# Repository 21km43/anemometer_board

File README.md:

# Anemometer board

# Requirements

- [KiCAD 9.0](https://kicad.org)
- [ESP32-C3-DevBoard](https://github.com/21km43/ESP32-C3-DevBoard)

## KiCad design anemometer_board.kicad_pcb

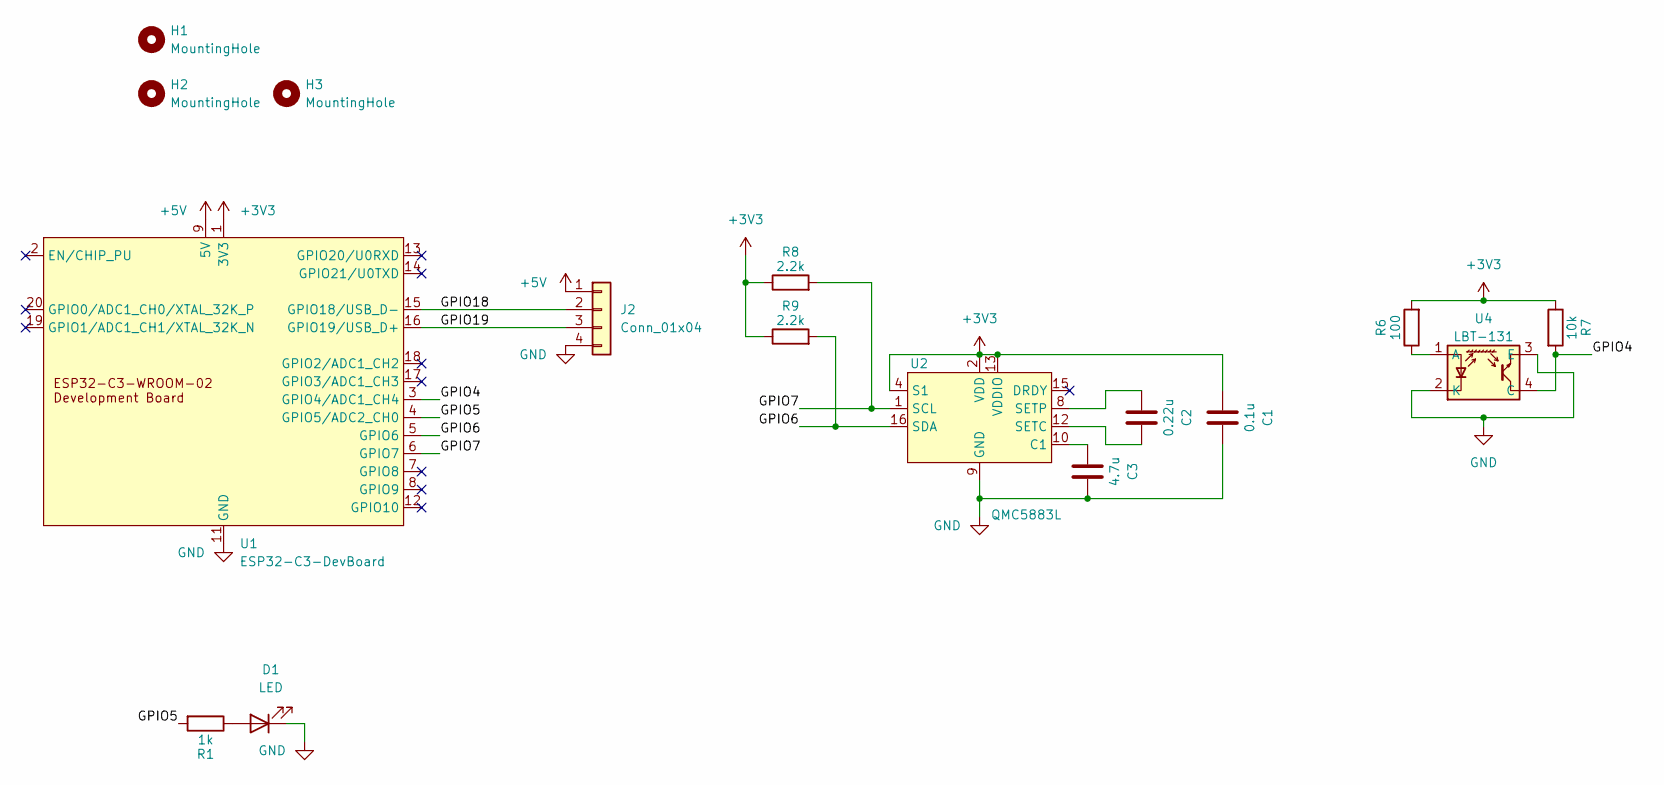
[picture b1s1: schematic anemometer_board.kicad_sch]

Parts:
C1: 0.1u; C_0402_1005Metric; LCSC C1525
C2: 0.22u; C_0402_1005Metric; LCSC C16772
C3: 4.7u; C_0402_1005Metric; LCSC C23733
D1: LED; LED_D5.0mm
H1, H2, H3: MountingHole; MountingHole_3.2mm_M3
J2: Conn_01x04; JST_XH_S4B-XH-A_1x04_P2.50mm_Horizontal
R1: 1k; R_Axial_DIN0207_L6.3mm_D2.5mm_P7.62mm_Horizontal; LCSC C11702
R6: 100; R_Axial_DIN0207_L6.3mm_D2.5mm_P10.16mm_Horizontal; LCSC C25076
R7: 10k; R_Axial_DIN0207_L6.3mm_D2.5mm_P10.16mm_Horizontal; LCSC C25744
R8, R9: 2.2k; R_0402_1005Metric; LCSC C25879
U1: ESP32-C3-DevBoard
U2: QMC5883L; LGA-16_3x3mm_P0.5mm; LCSC C976032
U4: LBT-131

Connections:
+3V3: C1.1, R6.2, R7.1, R8.1, R9.1, U1.1 (3V3), U2.2 (VDD), U2.4 (S1), U2.13 (VDDIO)
+5V: J2.1, U1.9 (5V)
/GPIO4: R7.2, U1.3 (GPIO4/ADC1_CH4), U4.4 (C)
/GPIO5: R1.2, U1.4 (GPIO5/ADC2_CH0)
/GPIO6: R9.2, U1.5 (GPIO6), U2.16 (SDA)
/GPIO7: R8.2, U1.6 (GPIO7), U2.1 (SCL)
/GPIO18: J2.2, U1.15 (GPIO18/USB_D-)
/GPIO19: J2.3, U1.16 (GPIO19/USB_D+)
GND: C1.2, C3.2, D1.1 (K), J2.4, U1.10 (GND), U1.11 (GND), U2.9 (GND), U2.11 (GND), U4.2 (K), U4.3 (E)
unnamed: D1.2 (A), R1.1
unnamed: C3.1, U2.10 (C1)
unnamed: C2.2, U2.12 (SETC)
unnamed: C2.1, U2.8 (SETP)
unnamed: R6.1, U4.1 (A)

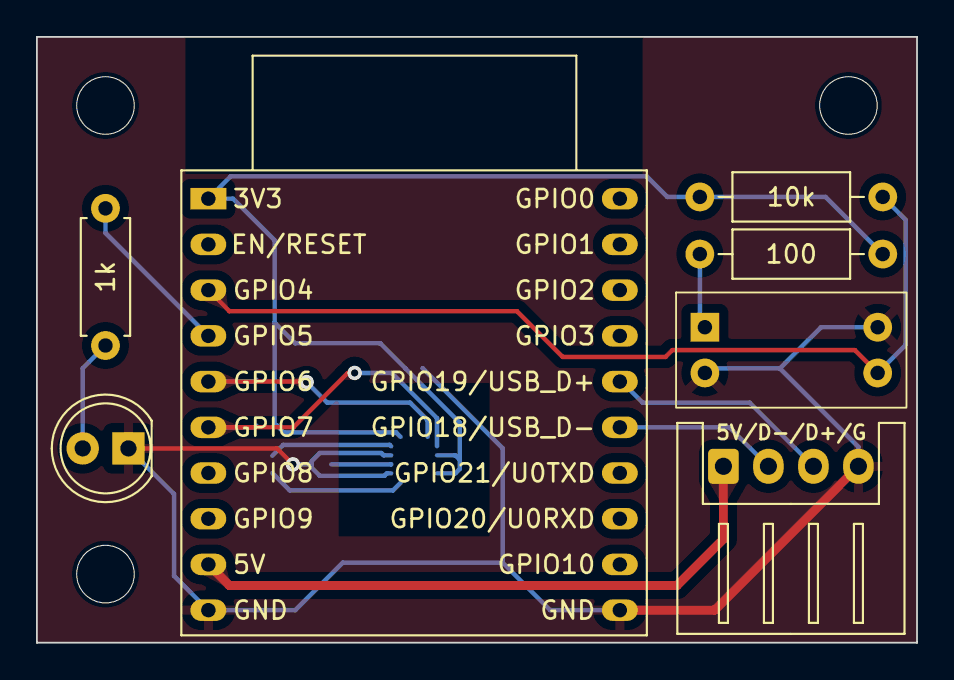
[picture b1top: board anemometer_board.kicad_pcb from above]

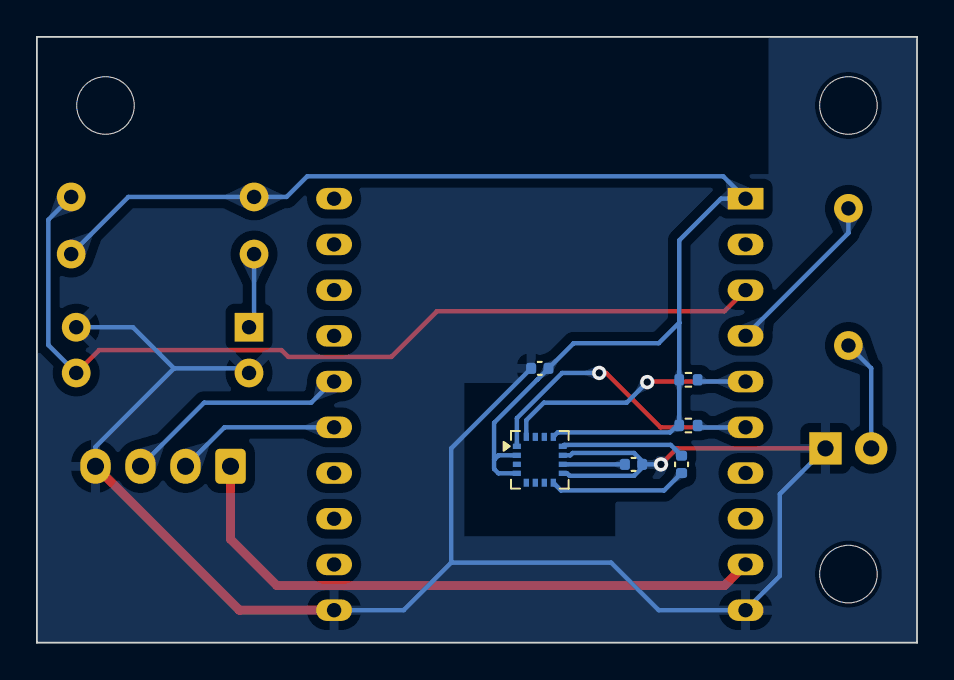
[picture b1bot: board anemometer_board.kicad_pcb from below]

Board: 2 copper layers, 48.9 x 33.7 mm, 16 parts (6 on the bottom side), 14 nets.

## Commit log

2025-03-23 fix gitignore
